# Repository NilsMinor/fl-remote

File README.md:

# FireLight Remote
A smart bluetooth low energy remote based on a nrf52 module with touch keys and a gyro sensor.

| Top view  | Bottom view  |
|--------|----------------|
|    | |

## Introduction
This board is based on a nrf52832 module from Minew (MS50SFB). It is designed as a remote to support the FireLight mesh as a special control node. However, as it is a normal nrf52 chipset it also supports Zephyr or other IoT frameworks. Checkout the nordic website for more software information.

## Features

The board comes with the following features:
- Small overall design (53 mm x 75 mm x 12 mm)
- Single PCB design with panel break off tabs
- nrf52832 module (MS50SFB) with onboard antenna
- 7 touch keys with 3 channel touch wheel based on the AT42QT2120
- 16 reverse mounted LEDs powerd by two TLC59108
- ICM-20600 6-Axis MEMS Motion tracking sensor 
- CP2104 USB to Uart converter
- Integrated single cell LiPo Charger (MCP73832)
- Most pats from JLCPCB parts library

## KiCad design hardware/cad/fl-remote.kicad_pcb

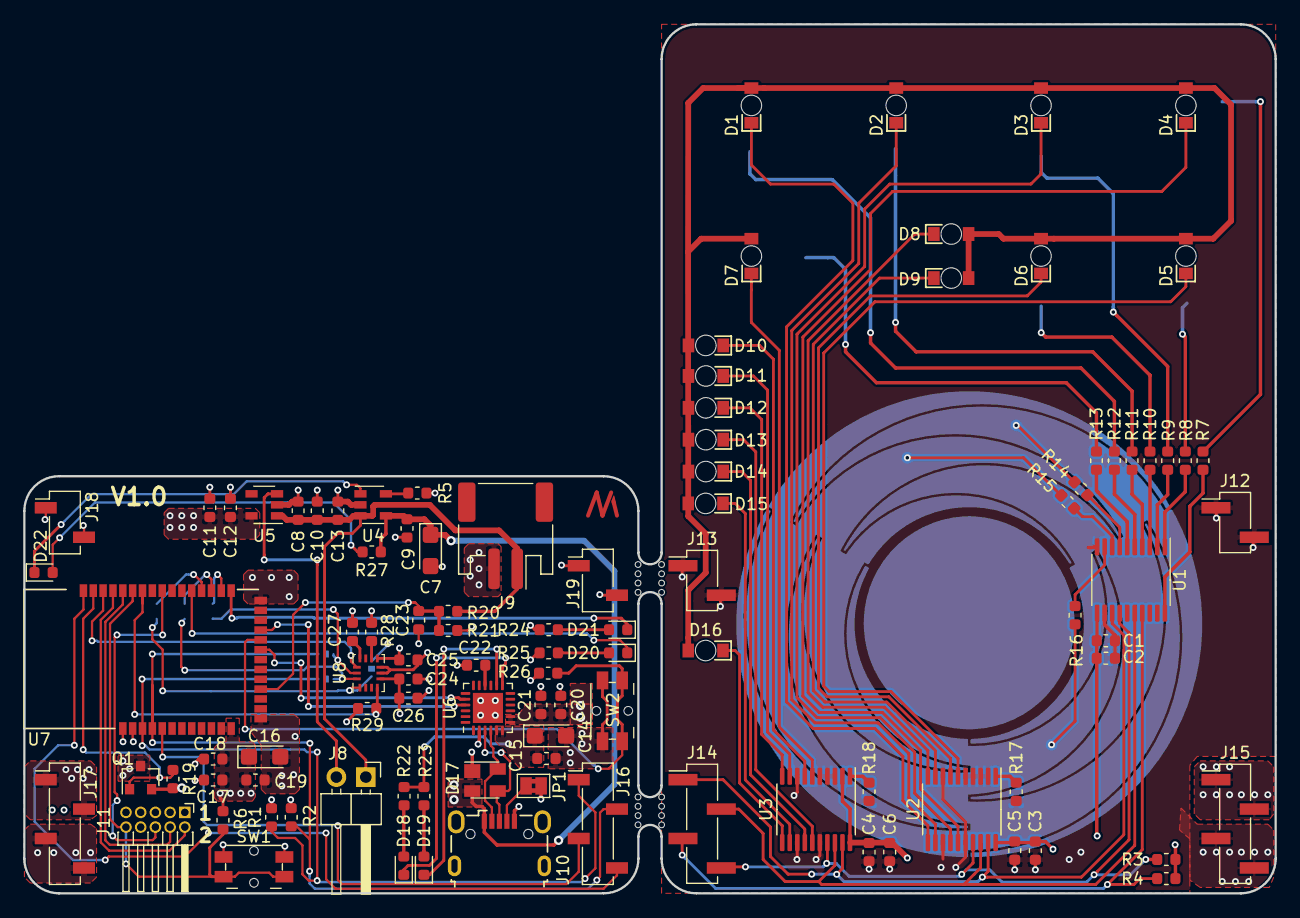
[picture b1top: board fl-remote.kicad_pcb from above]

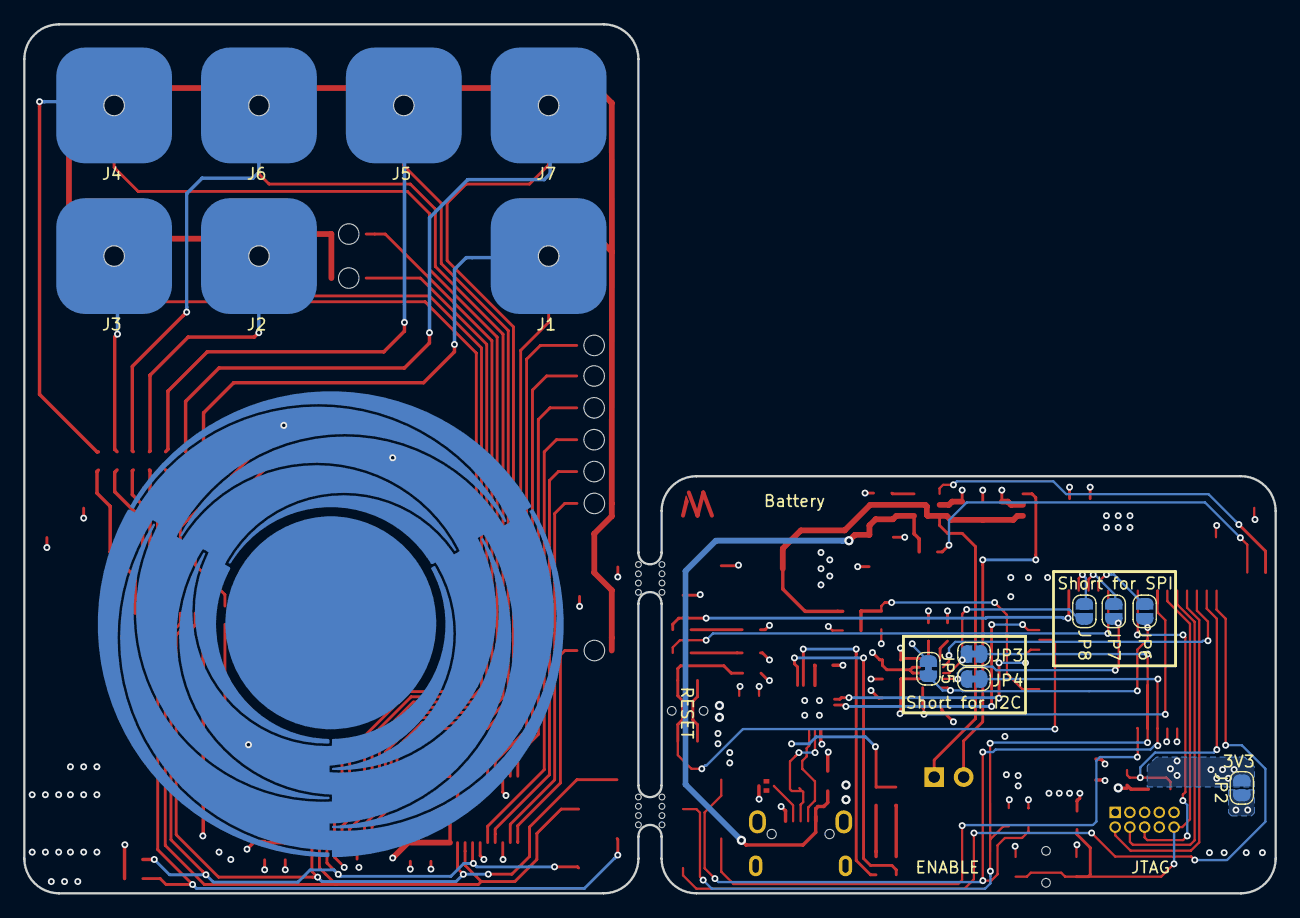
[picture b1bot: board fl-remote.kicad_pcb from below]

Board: 4 copper layers, 108.0 x 75.0 mm, 117 parts (14 on the bottom side), 87 nets.

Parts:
C1, C3, C4, C8, C11, C13, C17, C18, C20, C22, C25: 10u; C_0603_1608Metric
C2, C5, C6, C9, C10, C12, C15, C19, C21, C24, C26: 100n; C_0603_1608Metric
C7, C14, C16: 10u; CP_EIA-3216-18_Kemet-A
C23: 1n; C_0603_1608Metric
C27: 10n; C_0603_1608Metric
D1, D2, D3, D4, D5, D6, D7, D8, D9, D10, D11, D12, D13, D14, D15, D16: LED; 156125BS57000
D17: SP0503BAHT; SOT-143
D18, D19, D20, D21, D22: LED; LED_0603_1608Metric
J1, J2, J3, J4, J5, J6, J7: Conn_01x01_Male; Touchpad
J8: Conn_01x02_Male; PinHeader_1x02_P2.54mm_Horizontal
J9: Conn_01x02_Female; JST_PH_S2B-PH-SM4-TB_1x02-1MP_P2.00mm_Horizontal
J10: USB_B_Micro; USB_Micro-B_Wuerth_629105150521
J11: Conn_02x05_Odd_Even; PinHeader_2x05_P1.27mm_Horizontal
J12, J13: Conn_01x02_Male; PinHeader_1x02_P2.54mm_Vertical_SMD_Pin1Left
J14, J15: Conn_01x04_Male; PinHeader_1x04_P2.54mm_Vertical_SMD_Pin1Left
J16, J17: Conn_01x04_Female; PinSocket_1x04_P2.54mm_Vertical_SMD_Pin1Left
J18, J19: Conn_01x02_Female; PinSocket_1x02_P2.54mm_Vertical_SMD_Pin1Left
JP1: Jumper_NC_Small; SolderJumper-2_P1.3mm_Bridged2Bar_Pad1.0x1.5mm
JP2, JP6, JP7, JP8: Jumper_NO_Small; SolderJumper-2_P1.3mm_Open_RoundedPad1.0x1.5mm
JP3, JP4, JP5: Jumper_NC_Small; SolderJumper-2_P1.3mm_Bridged_RoundedPad1.0x1.5mm
Q1: Q_PMOS_GSD; SOT-23
R1, R2, R3, R4, R6, R7, R8, R9, R10, R11, R12, R13, R14, R15, R16, R26: 4k7; R_0603_1608Metric
R5: 2k; R_0603_1608Metric
R17, R18: 750R; R_0603_1608Metric
R19, R28, R29: 10k; R_0603_1608Metric
R20: 806k; R_0603_1608Metric
R21: 2M; R_0603_1608Metric
R22, R23, R27: 1k; R_0603_1608Metric
R24, R25: 1k6; R_0603_1608Metric
SW1, SW2: SW_Push; Panasonic_EVQPUL_EVQPUC
U1: AT42QT2120-XU; TSSOP-20_4.4x6.5mm_P0.65mm
U2, U3: TLC59108xPW; TSSOP-20_4.4x6.5mm_P0.65mm
U4: MCP73832-2-OT; SOT-23-5
U5: AP2112K-3.3; SOT-23-5
U6: CP2104; QFN-24-1EP_4x4mm_P0.5mm_EP2.6x2.6mm
U7: MS50SFB2
U8: ICM-20600; Bosch_LGA-14_3x2.5mm_P0.5mm
U9: Logo_NM

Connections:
+3V3: C11.1, C12.2, C16.1, C17.1, C18.1, C19.2, C24.2, C25.1, C26.2, J11.1, JP2.1, Q1.2, R1.2, R2.2, R6.2, R19.2, R24.2, R25.2, R26.2, R28.2, R29.2, U5.5, U7.12, U8.5, U8.8
/B_3V3: J17.1, J17.2, JP2.2, Q1.3
/B_SCL: J16.2, JP4.2, R2.1, U7.4
/B_SDA: J16.1, JP3.2, R1.1, U7.3
/INT1: R29.1, U7.35, U8.4
/INT2: R28.1, U8.9
/MISO: JP6.2, U7.29
/MOSI: JP7.2, U7.28
/SCLK: JP8.2, U7.27
/T_GND: C1.2, C2.2, C3.2, C4.2, C5.2, C6.2, J12.1, J12.2, J13.1, J13.2, J15.3, J15.4, R17.1, R18.1, U1.10, U1.12, U2.2, U2.3, U2.4, U2.5, U2.8, U2.13, U2.16, U3.3, U3.4, U3.5, U3.8, U3.13, U3.16
/T_SCL: J14.2, U1.16, U2.18, U3.18
/T_SDA: J14.1, U1.13, U2.19, U3.19
/T_VDD: C1.1, C2.1, C3.1, C4.1, C5.1, C6.1, J15.1, J15.2, R3.2, R4.2, U1.11, U2.20, U3.2, U3.20
/ble/AIN0: C23.1, R20.1, R21.2, U7.16
/ble/D9: D20.1, U7.30
/ble/D10: D21.1, U7.26
/ble/D11: R26.1, SW2.1, U7.21
/ble/P18: J11.6, U7.33
/ble/P21: J11.10, R6.1, SW1.1, U7.36
/ble/RXD: U6.21, U7.22
/ble/SWCLK: J11.4, U7.37
/ble/SWDIO: J11.2, U7.38
/imu/AD0_SDO: JP5.1, JP6.1, U8.1
/imu/SCL_SCLK: JP4.1, JP8.1, U8.13
/imu/SDA_SDI: JP3.1, JP7.1, U8.14
/power/EN: J8.2, U5.3
/power/VBAT: C8.1, C10.2, C13.1, J8.1, J9.1, R20.2, U4.3, U5.1
/touch/KEY3: J1.1, R13.1
/touch/KEY4: J7.1, R12.1
/touch/KEY5: J5.1, R11.1
/touch/KEY6: J2.1, R10.1
/touch/KEY7: J6.1, R9.1
/touch/KEY8: J3.1, R8.1
/touch/KEY9: J4.1, R7.1
/usb_to_uart/RXD_I: U6.20, U7.20
/usb_to_uart/USB_D+: D17.3, J10.3, U6.3
/usb_to_uart/USB_D-: D17.4, J10.2, U6.4
/~B_CHANGE: J16.3, U7.5
/~B_RESET: J16.4, U7.41
/~CS: U7.39, U8.12
/~ENABLE_3V3: Q1.1, R19.1, U7.40
/~T_CHANGE: J14.3, R4.1, U1.17
/~T_RESET: J14.4, R3.1, U1.14, U2.17, U3.17
GND: C7.2, C8.2, C9.1, C10.1, C11.2, C12.1, C13.2, C14.2, C15.1, C16.2, C17.2, C18.2, C19.1, C20.2, C21.1, C22.2, C23.2, C24.1, C25.2, C26.1, C27.1, D17.1, J9.2, J10.5, J10.6, J11.3, J11.5, J11.7, J11.9, J17.3, J17.4, J18.1, J18.2, J19.1, J19.2, JP1.2, JP5.2, R5.1, R21.1, SW1.2, SW2.2, U4.2, U5.2, U6.2, U6.25, U7.1, U7.2, U7.13, U7.25, U8.6, U8.7
unnamed: C22.1, U6.16
unnamed: C27.2, U8.11
unnamed: D1.1, U2.11
unnamed: D2.1, U2.12
unnamed: D3.1, U2.14
unnamed: D4.1, U2.15
unnamed: D5.1, U2.6
unnamed: D6.1, U2.7
unnamed: D7.1, U3.6
unnamed: D8.1, U2.10
unnamed: D9.1, U2.9
unnamed: D10.1, U3.7
unnamed: D11.1, U3.9
unnamed: D12.1, U3.10
unnamed: D13.1, U3.15
unnamed: D14.1, U3.14
unnamed: D15.1, U3.12
unnamed: D16.1, U3.11
unnamed: D18.1, U6.13
unnamed: D18.2, R22.1
unnamed: D19.1, U6.14
unnamed: D19.2, R23.1
unnamed: D20.2, R24.1
unnamed: D21.2, R25.1
unnamed: D22.1, U4.1
unnamed: D22.2, R27.1
unnamed: J10.4, JP1.1
unnamed: R5.2, U4.5
unnamed: R7.2, U1.20
unnamed: R8.2, U1.1
unnamed: R9.2, U1.2
unnamed: R10.2, U1.3
unnamed: R11.2, U1.4
unnamed: R12.2, U1.5
unnamed: R13.2, U1.6
unnamed: R14.2, U1.7
unnamed: R15.2, U1.8
unnamed: R16.2, U1.9
unnamed: R17.2, U2.1
unnamed: R18.2, U3.1
VAA: C14.1, C15.2, R22.2, R23.2, U6.5, U6.6
VBUS: C7.1, C9.2, C20.1, C21.2, D17.2, J10.1, R27.2, U4.4, U6.7, U6.8
VD: D1.2, D2.2, D3.2, D4.2, D5.2, D6.2, D7.2, D8.2, D9.2, D10.2, D11.2, D12.2, D13.2, D14.2, D15.2, D16.2

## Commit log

2020-11-26 added first hardware files
